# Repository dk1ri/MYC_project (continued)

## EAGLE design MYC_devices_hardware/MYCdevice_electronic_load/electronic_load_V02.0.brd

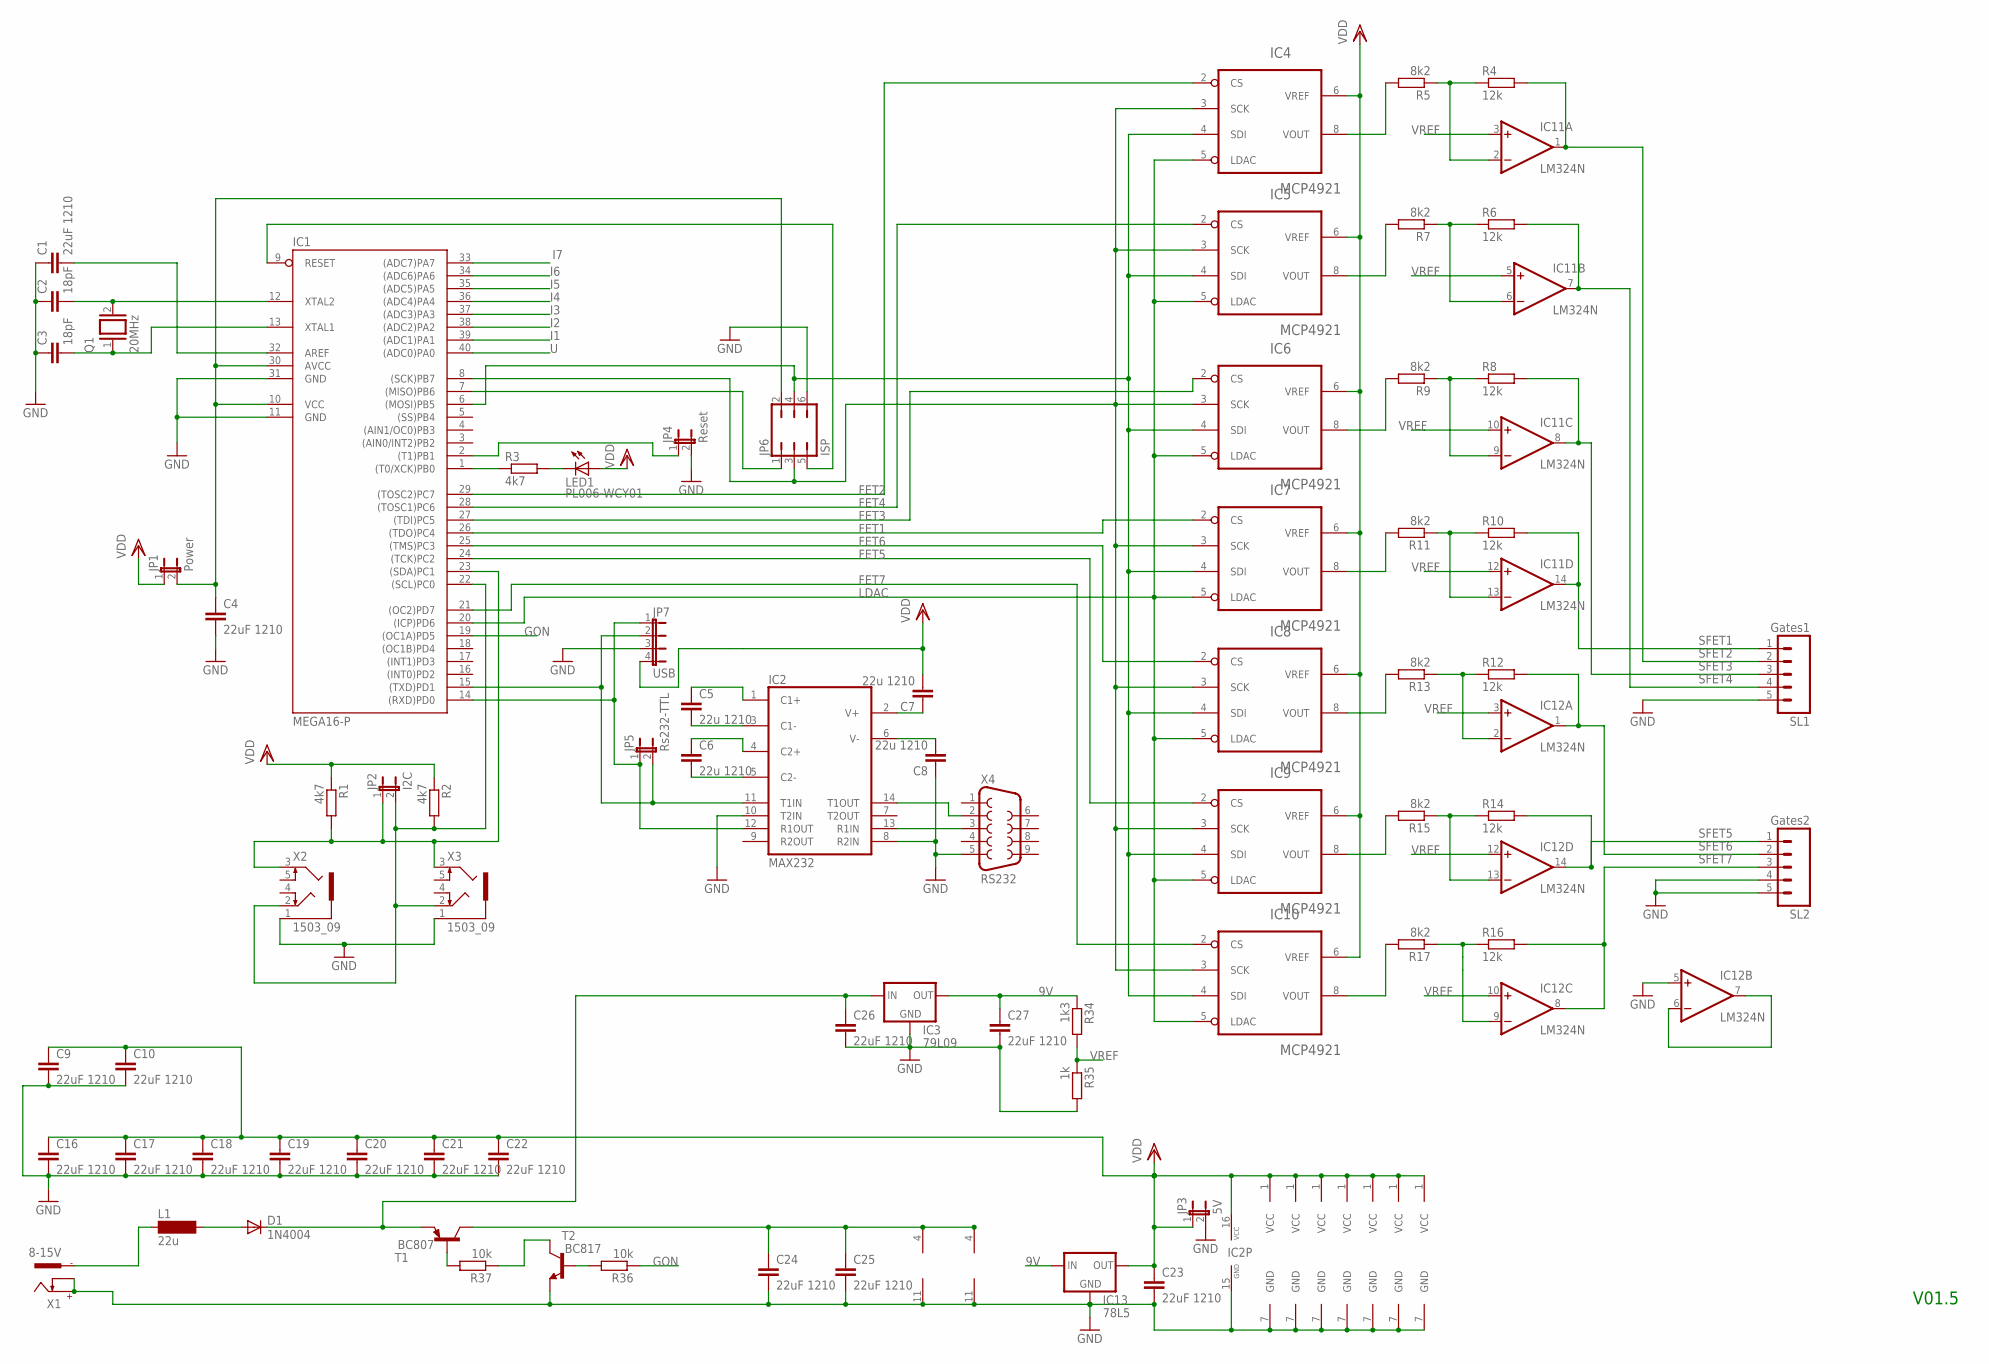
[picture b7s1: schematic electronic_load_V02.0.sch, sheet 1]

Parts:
C1, C4, C9, C10, C16, C17, C18, C19, C20, C21, C22, C23, C24, C25, C26, C27: 22uF 1210; C1206
C2, C3: 18pF; C025-025X050
C5, C6, C7, C8: 22u 1210; C1206
D1: 1N4004; DO41-10
IC1: MEGA16-P; DIL40
IC2: MAX232; DIL16
IC3: 79L09; 78LXX
IC4, IC5, IC6, IC7, IC8, IC9, IC10: MCP4921; DIL08
IC11, IC12: LM324N; DIL14
IC13: 78L5; 78LXX
JP1: Power; JP1
JP2: I2C; JP1
JP3: 5V; JP1
JP4: Reset; JP1
JP5: Rs232-TTL; JP1
JP6: ISP; JP3Q
JP7: USB; JP4
L1: 22u; MS85
LED1: PL006-WCY01; SOT23
Q1: 20MHz; QS
R1, R2: 4k7; 0207/2V
R3: 4k7; R1206
R4, R6, R8, R10, R12, R14, R16: 12k; R1206
R5, R7, R9, R11, R13, R15, R17: 8k2; R1206
R34: 1k3; R1206
R35: 1k; R1206
R36, R37: 10k; R1206
SL1: Gates1; 05P
SL2: Gates2; 05P
T1: BC807; SOT23-BEC
T2: BC817; SOT23-BEC
X1: 8-15V; 737992-5
X2, X3: 1503_09
X4: RS232; F09H

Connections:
9V: C27.1, IC3.OUT, IC13.IN, R34.1
C13: C5.1, IC2.1 (C1+)
FET1: IC1.26 ((TDO)PC4), IC7.2 (CS)
FET2: IC1.29 ((TOSC2)PC7), IC4.2 (CS)
FET3: IC1.27 ((TDI)PC5), IC6.2 (CS)
FET4: IC1.28 ((TOSC1)PC6), IC5.2 (CS)
FET5: IC1.24 ((TCK)PC2), IC9.2 (CS)
FET6: IC1.25 ((TMS)PC3), IC8.2 (CS)
FET7: IC1.21 ((OC2)PD7), IC10.2 (CS)
GND: C1.1, C2.1, C3.1, C4.2, C8.1, C9.2, C10.2, C16.2, C17.2, C18.2, C19.2, C20.2, C21.2, C22.2, C23.2, C24.2, C25.2, C26.2, C27.2, IC1.11 (GND), IC1.31 (GND), IC2.8 (R2IN), IC2.10 (T2IN), IC2.15 (GND), IC3.GND, IC4.7 (GND), IC5.7 (GND), IC6.7 (GND), IC7.7 (GND), IC8.7 (GND), IC9.7 (GND), IC10.7 (GND), IC11.11 (V-), IC12.5 (+IN), IC12.11 (V-), IC13.GND, JP3.2, JP4.2, JP6.6, JP7.3, R35.2, SL1.5, SL2.4, SL2.5, T2.E, X1.+, X1.K, X2.1, X3.1, X4.5; also elsewhere on the board
GON: IC1.19 ((OC1A)PD5), R36.1
I1: IC1.39 ((ADC1)PA1); also elsewhere on the board
I2: IC1.38 ((ADC2)PA2); also elsewhere on the board
I3: IC1.37 ((ADC3)PA3); also elsewhere on the board
I4: IC1.36 ((ADC4)PA4); also elsewhere on the board
I5: IC1.35 ((ADC5)PA5); also elsewhere on the board
I6: IC1.34 ((ADC6)PA6); also elsewhere on the board
I7: IC1.33 ((ADC7)PA7); also elsewhere on the board
LDAC: IC1.20 ((ICP)PD6), IC4.5 (LDAC), IC5.5 (LDAC), IC6.5 (LDAC), IC7.5 (LDAC), IC8.5 (LDAC), IC9.5 (LDAC), IC10.5 (LDAC)
unnamed: IC1.14 ((RXD)PD0), IC2.12 (R1OUT), JP5.1, JP7.1
unnamed: C6.2, IC2.5 (C2-)
unnamed: C4.1, IC1.10 (VCC), IC1.30 (AVCC), JP1.2, JP6.2
unnamed: IC1.23 ((SDA)PC1), JP2.1, R1.2, X2.3, X3.3
unnamed: IC1.15 ((TXD)PD1), IC2.11 (T1IN), JP5.2, JP7.2
unnamed: L1.1, X1.-1
unnamed: IC2.13 (R1IN), X4.3
unnamed: IC6.8 (VOUT), R9.2
unnamed: D1.A, L1.2
unnamed: C6.1, IC2.4 (C2+)
unnamed: C5.2, IC2.3 (C1-)
unnamed: IC1.7 ((MISO)PB6), JP6.1
unnamed: C7.1, IC2.2 (V+)
unnamed: C8.2, IC2.6 (V-)
unnamed: IC1.9 (RESET), JP6.5
unnamed: C2.2, IC1.12 (XTAL2), Q1.2
unnamed: IC1.6 ((MOSI)PB5), IC4.4 (SDI), IC5.4 (SDI), IC6.4 (SDI), IC7.4 (SDI), IC8.4 (SDI), IC9.4 (SDI), IC10.4 (SDI), JP6.4
unnamed: IC7.8 (VOUT), R11.2
unnamed: IC1.22 ((SCL)PC0), JP2.2, R2.2, X2.2, X3.2
unnamed: IC8.8 (VOUT), R13.2
unnamed: IC9.8 (VOUT), R15.2
unnamed: IC1.8 ((SCK)PB7), IC4.3 (SCK), IC5.3 (SCK), IC6.3 (SCK), IC7.3 (SCK), IC8.3 (SCK), IC9.3 (SCK), IC10.3 (SCK), JP6.3
unnamed: IC4.8 (VOUT), R5.2
unnamed: IC2.14 (T1OUT), X4.2
unnamed: C1.2, IC1.32 (AREF)
unnamed: IC11.13 (-IN), R10.1, R11.1
unnamed: C3.2, IC1.13 (XTAL1), Q1.1
unnamed: IC11.9 (-IN), R8.1, R9.1
unnamed: IC10.8 (VOUT), R17.2
unnamed: IC12.13 (-IN), R14.1, R15.1
unnamed: IC1.1 ((T0/XCK)PB0), R3.1
unnamed: LED1.3 (C), R3.2
unnamed: IC1.2 ((T1)PB1), JP4.1
unnamed: IC5.8 (VOUT), R7.2
unnamed: C26.1, D1.C, IC3.IN, T1.E
unnamed: IC12.2 (-IN), R12.1, R13.1
unnamed: IC12.9 (-IN), R16.1, R17.1
unnamed: C24.1, C25.1, IC11.4 (V+), IC12.4 (V+), T1.C
unnamed: R37.2, T1.B
unnamed: R37.1, T2.C
unnamed: R36.2, T2.B
unnamed: IC11.6 (-IN), R6.1, R7.1
unnamed: IC11.2 (-IN), R4.1, R5.1
unnamed: IC12.6 (-IN), IC12.7 (OUT)
SFET1: IC11.14 (OUT), R10.2, SL1.1
SFET2: IC11.1 (OUT), R4.2, SL1.2
SFET3: IC11.8 (OUT), R8.2, SL1.3
SFET4: IC11.7 (OUT), R6.2, SL1.4
SFET5: IC12.14 (OUT), R14.2, SL2.1
SFET6: IC12.1 (OUT), R12.2, SL2.2
SFET7: IC12.8 (OUT), R16.2, SL2.3
U: IC1.40 ((ADC0)PA0); also elsewhere on the board
VDD: C7.2, C9.1, C10.1, C16.1, C17.1, C18.1, C19.1, C20.1, C21.1, C22.1, C23.1, IC2.16 (VCC), IC4.1 (VCC), IC4.6 (VREF), IC5.1 (VCC), IC5.6 (VREF), IC6.1 (VCC), IC6.6 (VREF), IC7.1 (VCC), IC7.6 (VREF), IC8.1 (VCC), IC8.6 (VREF), IC9.1 (VCC), IC9.6 (VREF), IC10.1 (VCC), IC10.6 (VREF), IC13.OUT, JP1.1, JP3.1, JP7.4, LED1.1 (A), R1.1, R2.1; also elsewhere on the board
VREF: IC11.3 (+IN), IC11.5 (+IN), IC11.10 (+IN), IC11.12 (+IN), IC12.3 (+IN), IC12.10 (+IN), IC12.12 (+IN), R34.2, R35.1

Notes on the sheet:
V01.5

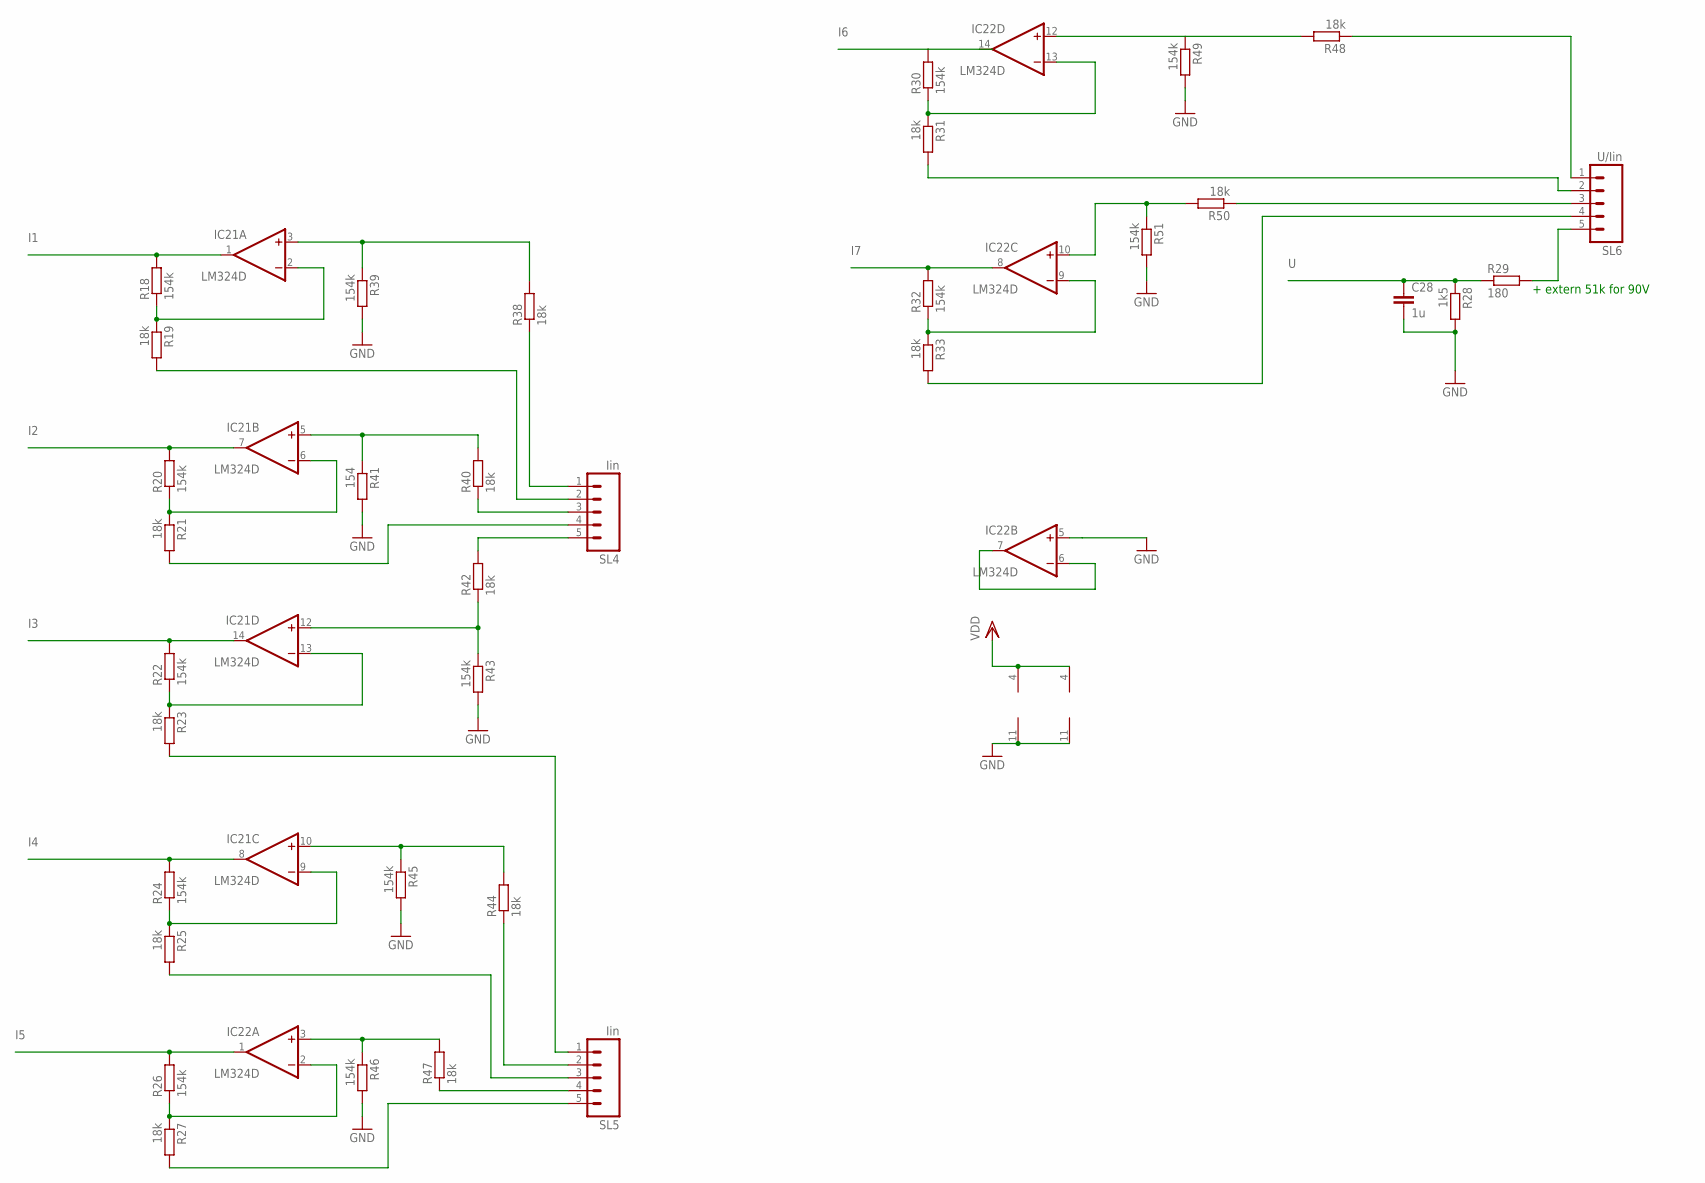
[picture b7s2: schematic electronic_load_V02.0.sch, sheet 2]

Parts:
C28: 1u; C1206
IC21, IC22: LM324D; SO14
R18, R20, R22, R24, R26, R30, R32, R39, R43, R45, R46, R49, R51: 154k; M1206
R19, R21, R23, R25, R27, R31, R33, R40, R42, R44, R47, R48, R50: 18k; M1206
R28: 1k5; R1206
R29: 180; R1206
R38: 18k; R1206
R41: 154; M1206
SL4, SL5: Iin; 05P
SL6: U/Iin; 05P

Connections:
GND: C28.2, IC21.11 (V-), IC22.5 (+IN), IC22.11 (V-), R28.2, R39.2, R41.2, R43.2, R45.2, R46.2, R49.2, R51.2; also elsewhere on the board
I1: IC21.1 (OUT), R18.2; also elsewhere on the board
I2: IC21.7 (OUT), R20.2; also elsewhere on the board
I3: IC21.14 (OUT), R22.2; also elsewhere on the board
I4: IC21.8 (OUT), R24.2; also elsewhere on the board
I5: IC22.1 (OUT), R26.2; also elsewhere on the board
I6: IC22.14 (OUT), R30.2; also elsewhere on the board
I7: IC22.8 (OUT), R32.2; also elsewhere on the board
unnamed: IC21.2 (-IN), R18.1, R19.1
unnamed: IC22.6 (-IN), IC22.7 (OUT)
unnamed: R29.2, SL6.5
unnamed: R21.2, SL4.4
unnamed: IC21.6 (-IN), R20.1, R21.1
unnamed: IC22.9 (-IN), R32.1, R33.1
unnamed: IC22.13 (-IN), R30.1, R31.1
unnamed: IC21.13 (-IN), R22.1, R23.1
unnamed: IC21.10 (+IN), R44.2, R45.1
unnamed: IC21.9 (-IN), R24.1, R25.1
unnamed: IC22.2 (-IN), R26.1, R27.1
unnamed: R47.1, SL5.4
unnamed: IC21.5 (+IN), R40.2, R41.1
unnamed: R48.1, SL6.1
unnamed: R31.2, SL6.2
unnamed: R25.2, SL5.3
unnamed: R27.2, SL5.5
unnamed: R38.1, SL4.1
unnamed: R40.1, SL4.3
unnamed: IC21.3 (+IN), R38.2, R39.1
unnamed: R42.2, SL4.5
unnamed: R19.2, SL4.2
unnamed: R44.1, SL5.2
unnamed: IC22.3 (+IN), R46.1, R47.2
unnamed: IC22.12 (+IN), R48.2, R49.1
unnamed: R50.1, SL6.3
unnamed: R23.2, SL5.1
unnamed: IC21.12 (+IN), R42.1, R43.1
unnamed: R33.2, SL6.4
unnamed: IC22.10 (+IN), R50.2, R51.1
U: C28.1, R28.1, R29.1; also elsewhere on the board
VDD: IC21.4 (V+), IC22.4 (V+); also elsewhere on the board

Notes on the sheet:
+ extern 51k for 90V

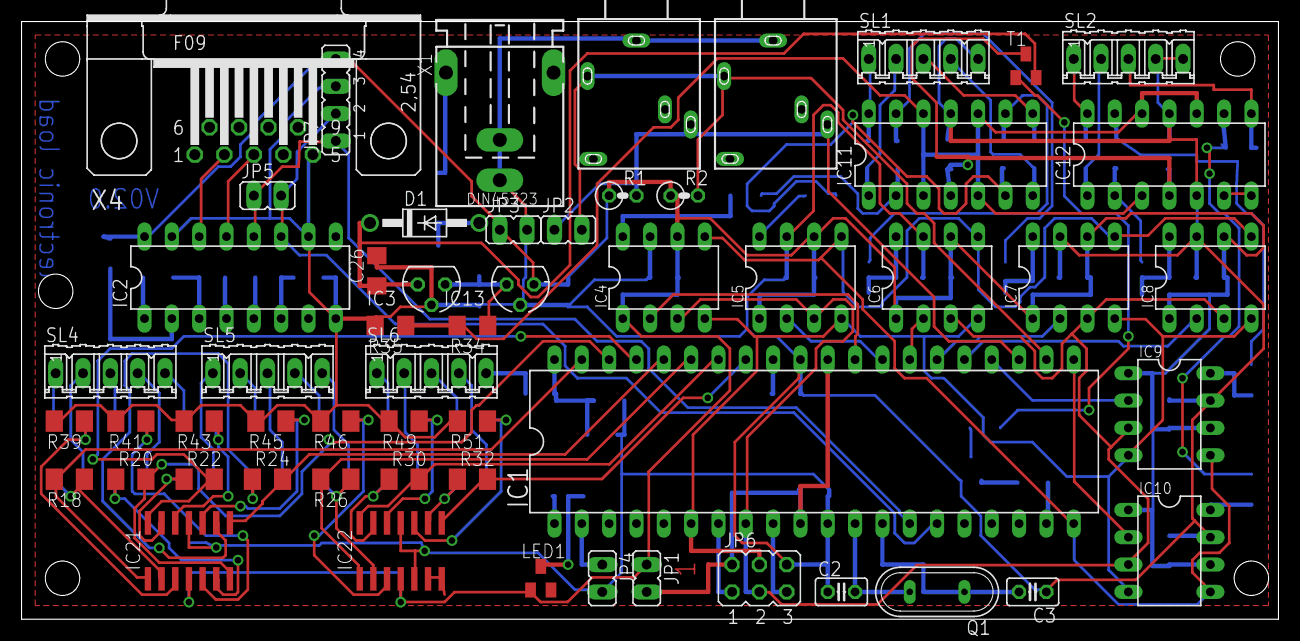
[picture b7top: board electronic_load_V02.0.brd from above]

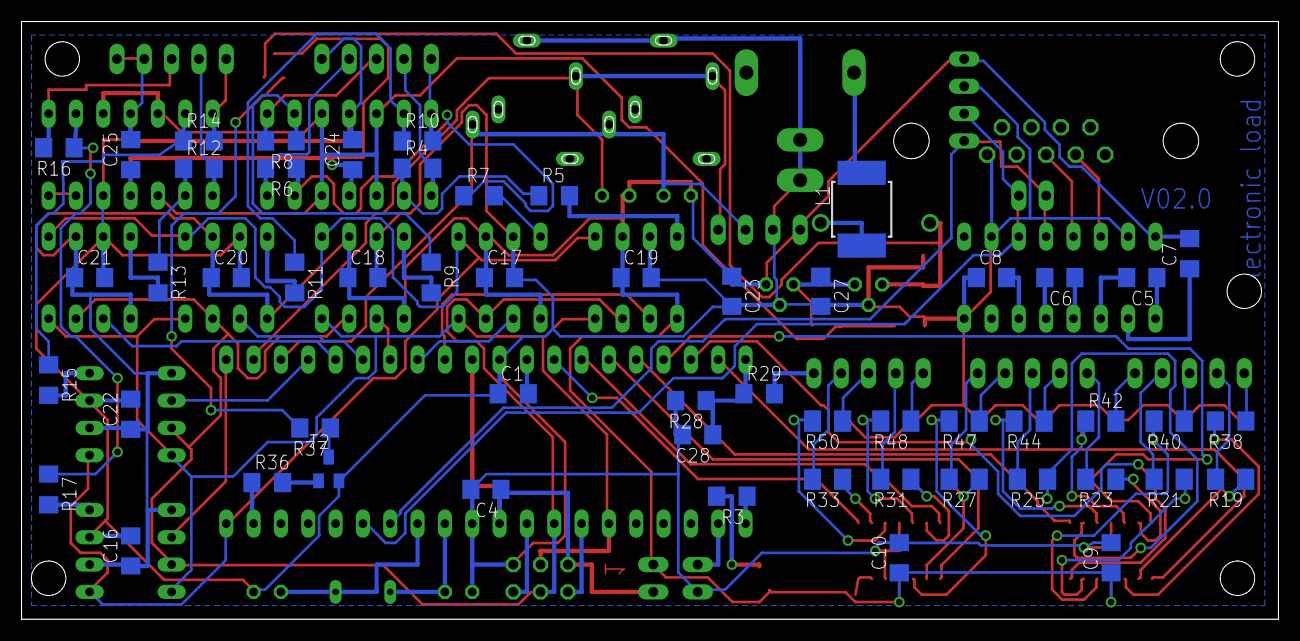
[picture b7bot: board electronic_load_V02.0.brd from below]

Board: 2 copper layers, 116.8 x 55.5 mm, 111 parts (55 on the bottom side), 103 nets.

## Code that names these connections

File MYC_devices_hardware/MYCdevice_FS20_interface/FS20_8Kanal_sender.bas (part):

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' I2C
'-----------------------------------------------------------------------
' Inputs: Reset: Pin B.0
' Outputs: PD2 - PD7, PB0, PB1
' For announcements and rules see Data section at the end
'
'-----------------------------------------------------------------------
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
